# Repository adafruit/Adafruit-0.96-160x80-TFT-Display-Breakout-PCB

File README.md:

## Adafruit 0.96" 160x80 TFT LCD Display Breakout PCB

<a href="http://www.adafruit.com/products/3533"><br/>
Click here to purchase one from the Adafruit shop</a>

PCB files for the Adafruit 0.96" 160x80 TFT Display Breakout. Format is EagleCAD schematic and board layout

For more details, check out the product pages at
* https://www.adafruit.com/products/3533

### Description

Say hello to our 0.96" 160x80 Color TFT Display w/ MicroSD Card Breakout – we think it's T-F-Terrific! It's the size of your thumbnail, with glorious 160x80 pixel color. This very very small display is only 0.96" diagonal, packed with RGB pixels, for making very small high-density displays.

This lovely little display breakout is a great way to add a small, colorful and bright display to any project. Since the display uses 4-wire SPI to communicate and has its own pixel-addressable frame buffer, it can be used with every kind of microcontroller. Even a very small one with low memory and few pins available!

The 0.96" display has 160x80 color pixels. Unlike the low cost "Nokia 6110" and similar LCD displays, which are CSTN type and thus have poor color and slow refresh, this display is a true TFT! The TFT driver (ST7735R) can display full 16-bit color using our library code.

The breakout has the TFT display soldered on (it uses a delicate flex-circuit connector) as well as a ultra-low-dropout 3.3V regulator and a 3/5V level shifter so you can use it with 3.3V or 5V power and logic. We also had a little space so we placed a microSD card holder so you can easily load full color bitmaps from a FAT16/FAT32 formatted microSD card. **The microSD card is not included.**

### License

Adafruit invests time and resources providing this open source design, please support Adafruit and open-source hardware by purchasing products from [Adafruit](https://www.adafruit.com)!

Designed by Limor Fried/Ladyada for Adafruit Industries.

Creative Commons Attribution/Share-Alike, all text above must be included in any redistribution. See license.txt for additional details.

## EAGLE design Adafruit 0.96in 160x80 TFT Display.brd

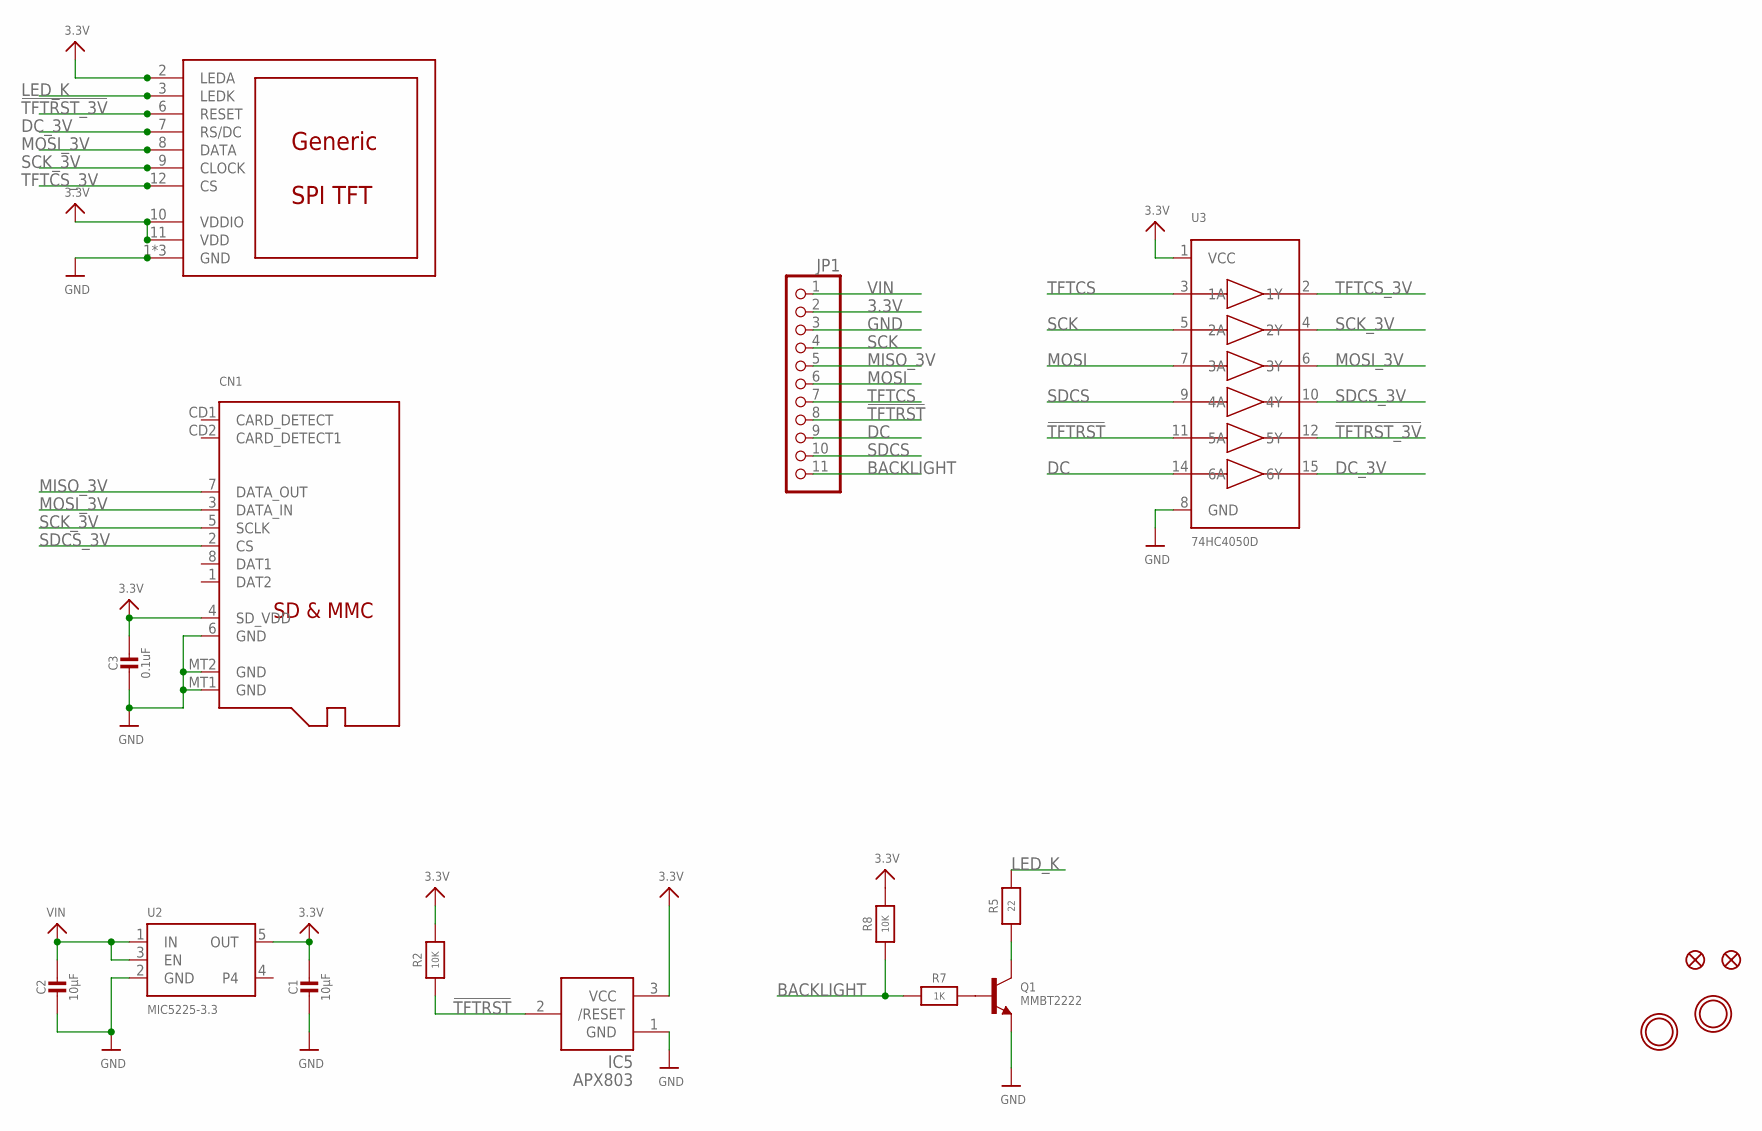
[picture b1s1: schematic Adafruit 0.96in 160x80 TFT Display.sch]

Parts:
C1, C2: 10µF; 0805-NO
C3: 0.1uF; 0805-NO
CN1: MICROSD
FID1, FID2: FIDUCIAL_1MM
IC5: APX803; SOT23
JP1: HEADER-1X11; 1X11_ROUND
Q1: MMBT2222; SOT23-WIDE
R2, R8: 10K; 0603-NO
R5: 22; 0603-NO
R7: 1K; 0603-NO
U2: MIC5225-3.3; SOT23-5
U3: 74HC4050D; SOIC16
U$2: DISP_LCD_0.9IN_160X80; TFT_0.96IN_160X80
U$9, U$10: MOUNTINGHOLE2.5; MOUNTINGHOLE_2.5_PLATED

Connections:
3.3V: C1.1, C3.1, CN1.4 (SD_VDD), IC5.3 (VCC), JP1.2, R2.2, R8.2, U2.5 (OUT), U3.1 (VCC), U$2.2 (LEDA), U$2.10 (VDDIO), U$2.11 (VDD)
!TFTRST: IC5.2 (/RESET), JP1.8, R2.1, U3.11 (5A)
!TFTRST_3V: U3.12 (5Y), U$2.6 (RESET)
BACKLIGHT: JP1.11, R7.1, R8.1
DC: JP1.9, U3.14 (6A)
DC_3V: U3.15 (6Y), U$2.7 (RS/DC)
GND: C1.2, C2.2, C3.2, CN1.6 (GND), CN1.MT1 (GND), CN1.MT2 (GND), IC5.1 (GND), JP1.3, Q1.2 (E), U2.2 (GND), U3.8 (GND), U$2.1 (GND), U$2.5 (GND), U$2.13 (GND)
LED_K: R5.2, U$2.3 (LEDK)
MISO_3V: CN1.7 (DATA_OUT), JP1.5
MOSI: JP1.6, U3.7 (3A)
MOSI_3V: CN1.3 (DATA_IN), U3.6 (3Y), U$2.8 (DATA)
unnamed: Q1.1 (B), R7.2
unnamed: Q1.3 (C), R5.1
SCK: JP1.4, U3.5 (2A)
SCK_3V: CN1.5 (SCLK), U3.4 (2Y), U$2.9 (CLOCK)
SDCS: JP1.10, U3.9 (4A)
SDCS_3V: CN1.2 (CS), U3.10 (4Y)
TFTCS: JP1.7, U3.3 (1A)
TFTCS_3V: U3.2 (1Y), U$2.12 (CS)
VIN: C2.1, JP1.1, U2.1 (IN), U2.3 (EN)

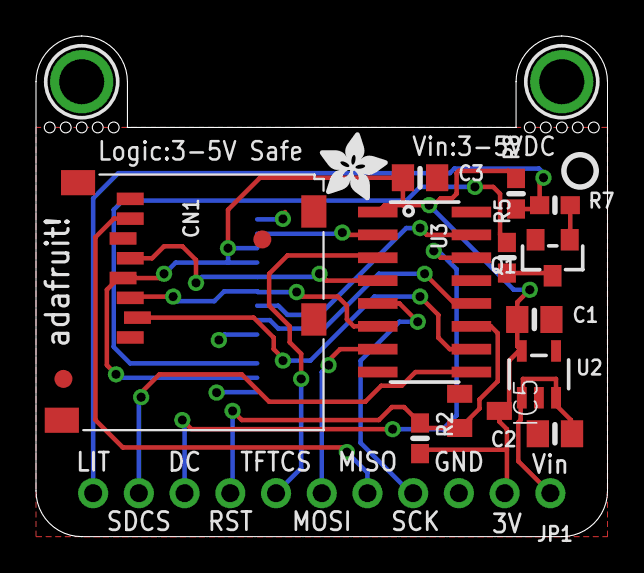
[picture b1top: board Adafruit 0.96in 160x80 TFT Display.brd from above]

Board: 2 copper layers, 31.8 x 27.8 mm, 20 parts (1 on the bottom side), 20 nets.

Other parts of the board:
U$4: MICROSD; ADAFRUIT_3.5MM
U$6: PCBFEAT-REV-040

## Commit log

2017-06-11 init
